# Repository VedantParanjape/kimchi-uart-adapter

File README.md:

# kimchi-uart-adapter

UART adapter for the kimichi micro SBC by GroupGets

## Schematics

## Reference

* Built upon design by [A13](https://github.com/a13-technologies/kimchi-uart-adapter)

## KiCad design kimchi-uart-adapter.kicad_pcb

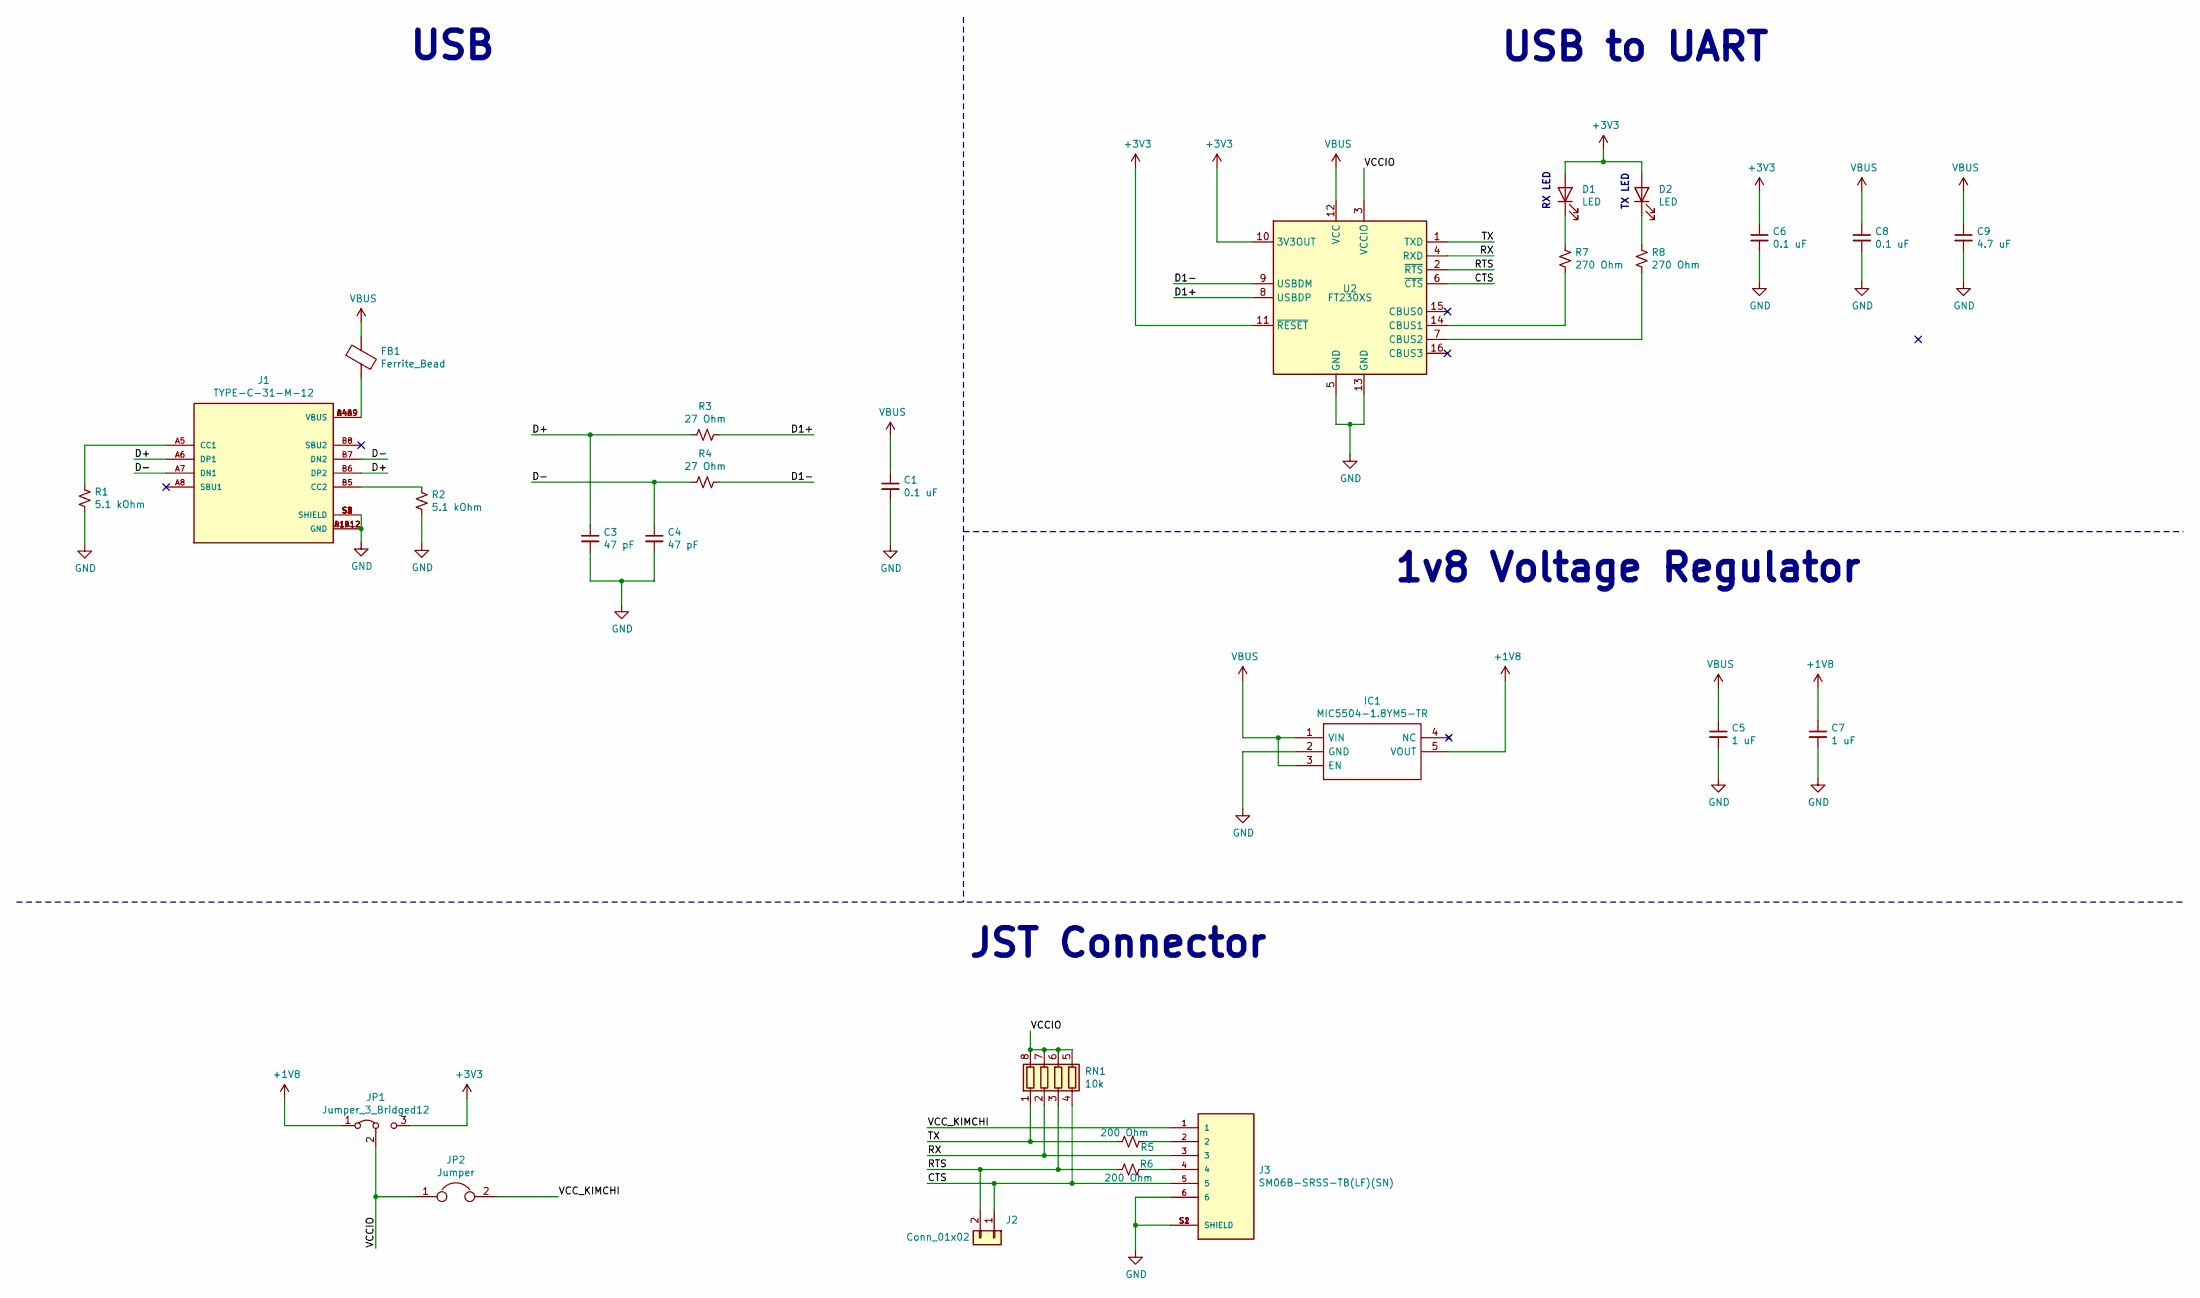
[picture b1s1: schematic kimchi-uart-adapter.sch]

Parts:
C1, C6, C8: 0.1 uF; C_0603_1608Metric
C3, C4: 47 pF; C_0603_1608Metric
C5, C7: 1 uF; C_0603_1608Metric
C9: 4.7 uF; C_0603_1608Metric
D1, D2: LED; LED_0603_1608Metric
FB1: Ferrite_Bead; R_0603_1608Metric
IC1: MIC5504-1.8YM5-TR; SOT95P280X130-5N; Manufacturer_Part_Number MIC5504-1.8YM5-TR; Mouser Part Number 998-MIC5504-1.8YM5TR
J1: TYPE-C-31-M-12; HRO_TYPE-C-31-M-12; PARTREV A
J2: Conn_01x02; PinHeader_1x02_P1.27mm_Vertical
J3: SM06B-SRSS-TB(LF)(SN); JST_SM06B-SRSS-TB(LF)(SN)
JP1: Jumper_3_Bridged12; SolderJumper-3_P1.3mm_Open_RoundedPad1.0x1.5mm_NumberLabels
JP2: Jumper; SolderJumper-2_P1.3mm_Open_RoundedPad1.0x1.5mm
R1, R2: 5.1 kOhm; R_0603_1608Metric
R3, R4: 27 Ohm; R_0603_1608Metric
R5, R6: 200 Ohm; R_0603_1608Metric
R7, R8: 270 Ohm; R_0603_1608Metric
RN1: 10k; R_Array_Convex_4x0603
U2: FT230XS; SSOP-16_3.9x4.9mm_P0.635mm

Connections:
+1V8: C7.1, IC1.5 (VOUT), JP1.1 (A)
+3V3: C6.1, D1.2 (A), D2.2 (A), JP1.3 (B), U2.10 (3V3OUT), U2.11 (~RESET)
/CTS: J2.1, J3.5, RN1.4 (R4.1), U2.6 (~CTS)
/D1+: R3.1, U2.8 (USBDP)
/D1-: R4.1, U2.9 (USBDM)
/D+: C3.1, J1.A6 (DP1), J1.B6 (DP2), R3.2
/D-: C4.1, J1.A7 (DN1), J1.B7 (DN2), R4.2
/RTS: J2.2, R6.2, RN1.3 (R3.1), U2.2 (~RTS)
/RX: J3.3, RN1.2 (R2.1), U2.4 (RXD)
/TX: R5.2, RN1.1 (R1.1), U2.1 (TXD)
/VCCIO: JP1.2 (C), JP2.1, RN1.5 (R4.2), RN1.6 (R3.2), RN1.7 (R2.2), RN1.8 (R1.2), U2.3 (VCCIO)
/VCC_KIMCHI: J3.1, JP2.2
GND: C1.2, C3.2, C4.2, C5.2, C6.2, C7.2, C8.2, C9.2, IC1.2 (GND), J1.A1B12 (GND), J1.B1A12 (GND), J1.S1 (SHIELD), J1.S2 (SHIELD), J1.S3 (SHIELD), J1.S4 (SHIELD), J3.6, J3.S1 (SHIELD), J3.S2 (SHIELD), R1.2, R2.2, U2.5 (GND), U2.13 (GND)
unnamed: D1.1 (K), R7.2
unnamed: D2.1 (K), R8.1
unnamed: FB1.2, J1.A4B9 (VBUS), J1.B4A9 (VBUS)
unnamed: J1.A5 (CC1), R1.1
unnamed: J1.B5 (CC2), R2.1
unnamed: J3.2, R5.1
unnamed: J3.4, R6.1
unnamed: R7.1, U2.14 (CBUS1)
unnamed: R8.2, U2.7 (CBUS2)
VBUS: C1.1, C5.1, C8.1, C9.1, FB1.1, IC1.1 (VIN), IC1.3 (EN), U2.12 (VCC)

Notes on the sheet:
USB
USB to UART
RX LED
TX LED
1v8 Voltage Regulator
JST Connector

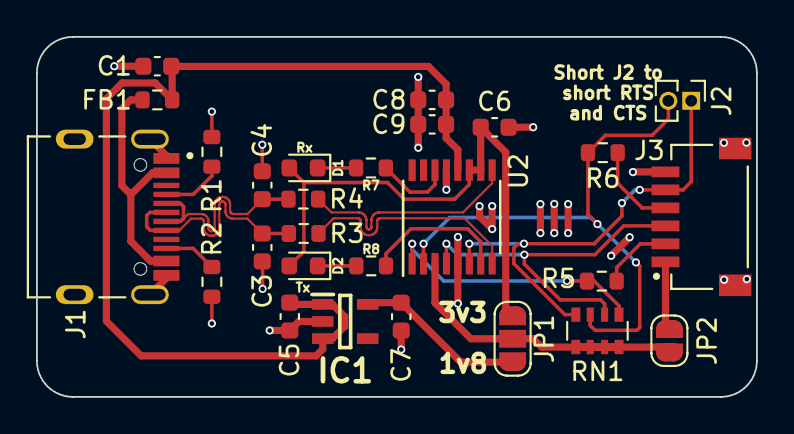
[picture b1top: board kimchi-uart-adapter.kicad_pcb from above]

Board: 2 copper layers, 40.0 x 20.0 mm, 27 parts (0 on the bottom side), 23 nets.

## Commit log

2021-05-29 Added kicad project, schematics half done
2021-05-29 Completed schematics
2021-05-29 Added LICENSE and README.md
2021-06-13 Completed partial routing
2021-06-19 Almost completed routing, waiting for fix to the resistor network issue. Also replaced model for TPD2E001 chip
2021-06-22 Completed routing
2021-07-10 Completed routing of uart lid
2021-07-12 Updated silkscreen text
2021-07-15 Fixed changes requested during review, added gerbers and render images
